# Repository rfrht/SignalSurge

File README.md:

# SignalSurge
This is an open source (check licensing [here](https://github.com/rfrht/SignalSurge/blob/main/LICENSE)) Bandpass filter for VHF and UHF amateur radio bands, with a selectable LNA and a sequencer. Designed using Eagle CAD 9.

# Why?
I live in a highly RF-polluted metropolitan area. One of these days, only FFS I have added a FM bandstop filter and I found that, contrary to my belief, my reception was **way better**! That means:

1. The front-end radio filtering is less than great (even being an expensive FT-991A)
2. Strong out of amateur band signals (and there's **plenty** of them) will desensitize your radio
3. By filtering out unwanted signals, you give more **dynamic range** to your radio, improving your reception.
4. [See for yourself here](https://www.reddit.com/r/amateurradio/comments/1gxahma/noticeable_improvement_in_ft991a_2m_rx_when_using/).

That said, the objective of this project is to remove as much as possible signals outside 2m and 70 cm bands (like: FM broadcasts, air band, commercial VHF & UHF, and everything else inbetween), ensuring that the precious front-end gain on the radio's built-in amplifier focuses on amateur band signals as much as possible.

I could buy a [300 EUR filter](https://antennas-amplifiers.com/double-2x200w-bandpass-filter-144-148mhz-430-450mhz/), but... man, that's expensive. So why not spend €3,000 worth of my own man-hours and parts to build one?

# Features
* Two **selectable** amateur band (2m and 70 cm) [bandpass filter](https://github.com/rfrht/SignalSurge/blob/main/rf-performance.md) weeds out signals, ensuring that the transceiver front-end focus its gain figures on inband signals only. That can be automated by making use of the Band Data (`TUN/LIN` port, pins `4` or `5`). Requires menu config 141 (`TUNER SELECT`) to be set as `LAMP`.
* **High performance** and selectable [low noise 15 dB amplifier](https://github.com/rfrht/SignalSurge/blob/main/rf-performance.md#amplifier-performance) (Infineon BFP460) after the bandpass filter, adding some oomph to weak signals
* Nearly **-70 dB of rejection** against the FM broadcast band
* The amplifier is **shut down when the radio is transmitting** by powering off its 5V rail (by cutting the regulator "Enable" line) to prevent any artifacts/ringing and damage. 
* Specialty RF relay allowing 50W in VHF/UHF frequencies to flow to the antenna with **low loss**, while keeping **[unparalleled isolation](https://www.reddit.com/r/rfelectronics/comments/1h5mthn/comment/m0de8n7/) (north of 60 dB)** to the downstream components
* Relay **default state (NC) is to bypass** radio directly to antenna, allowing the board to be safely powered off
* [TX Inhibit](https://github.com/rfrht/FT-991A/blob/master/understanding-ft-991a-tx-inhibit.md) logic outputs +13.8V to the FT-991A's TUN/LIN port whenever the delicate BPF/LNA chain is active, **preventing accidental** 50W transmissions into the low-power solid-state switches and filter chain
* **Static bleeding and small [surge protection](https://www.digikey.com/en/products/detail/eaton-electronics-division/0603ESDA2-TR2/3681416)** when switched to BPF/AMP
* [Via-Stitched Grounded Coplanar Waveguides (GCPW)](https://resources.altium.com/p/pros-and-cons-of-different-high-frequency-transmission-line-types) ensures strictly controlled 50-ohm impedance and suppresses parasitic radiative modes. Real-world proof: the board effortlessly handles **50 Watts** (+47 dBm) of 70cm RF on an open bench **without radiating** into the room or causing the dreaded "speaker buzz" in nearby unshielded subwoofers.
* A **[detachable miniature](https://github.com/rfrht/SignalSurge/blob/main/others/miniature-filter-board.jpg)** VHF BPF filter that [fits perfectly](https://github.com/rfrht/SignalSurge/blob/main/others/miniature-filter.jpg) in [RTL-SDR](https://www.rtl-sdr.com/rtl-sdr-com-broadcast-fm-band-stop-filter-88-108-mhz-reject-now-for-sale/) [FM bandstop cases](https://github.com/rfrht/SignalSurge/blob/main/others/encased-miniature-filter.jpg). **NOTE:** This filter DOES NOT withstand TX power; it will **fry** the inductor! Do not transmit on it.

## Library
Eagle custom component library [here](https://github.com/rfrht/FT991A-PAT/blob/master/Schematic/aarf.lbr). Ensure to **also** fetch the latest library version (and update in your Eagle) when checking out new code.

Bill of Materials (CSV format, DigiKey format) [here](https://github.com/rfrht/SignalSurge/blob/main/others/SS.csv). Notice that there's a full RF Inductor and Capacitor kit specified in the BOM - and that is **costly**. If you have the suitable RF L/C components, fine! Otherwise (like me), buy a proper one.

# Schematic: 

# Board layout
[Rev. E1 populated board](https://github.com/rfrht/SignalSurge/blob/main/others/ss-board-finished.jpg)

# BPF & Amplifier performance
Check the [test results](https://github.com/rfrht/SignalSurge/blob/main/rf-performance.md) page.

# Relay Logic
Check the [relay logic](https://github.com/rfrht/SignalSurge/blob/main/others/relay-logic.md) page.

# Test, troubleshooting steps & Specs
Yes - I have provided a [step by step testing and troubleshooting](https://github.com/rfrht/SignalSurge/blob/main/others/testing.md) guide!

# KNOWN ISSUES
**Ensure** to check the [Issues backlog](https://github.com/rfrht/SignalSurge/issues)

# JOURNEY
* Sep 18 - Updating the test figures. Successfully used the [TX INH](https://github.com/rfrht/FT-991A/blob/master/understanding-ft-991a-tx-inhibit.md) functionality at the radio. Released Rev. F.
* Sep 14 - Starting Rev. F. Changed "Bypass" and "VHF/UHF" selectors to input 5V in order to be able to use the [BCD decoders from FT-991 band data](https://hf5l.pl/en/1472-2/) at the TUN/LIN port. Added u.FL calibration pads.
* Sep 12 - Assembled board Rev. E1. Documented RF performance.
* Jun 06 - Improved UHF filter, making it narrower (50 to 30 MHz wide) and less lossy. Added another component in UHF schematic/board in order to allow for a fine tune capacitance of the coupling stage.
* May 28 - Fixed a gross error where a via shorted the VHF BPF final coupling stage. Removed ground pad on inductors at the detachable VHF BPF. Improved the radio signal trace at the first RF relay input. Updated component values for the 3-pole VHF filter (*in vivo* performed differently than the *in vitro*)
* May 04 - Replaced 3V regulator (was above its maximum rated) with a MIC5205. Removed a pulldown resistor in VHF line. Unified pulldowns on 10k and pulled lines limiters at 1k. Removed a pulldown between the NOR and AND logic ICs
* May 03 - Vibe-coded a new UHF filter with Gemini. Refactored the board, the filters, waveguides, soldermask, signal path
* May 01 - Starting Revision E. Vibe-coded a new VHF filter with Gemini
* Mar 19 - Removed two unneeded RF switches at the front-end: extra cost, complexity and insertion loss - unnecessarily, as the RF stage is handsomely isolated - and powered off during high power operations.
* Feb 28 - Found the need of a pulldown resistor in the VHF switch line. Refactored the CPW between the relays, hoping this tackle the high VSWR in 70 cm band.
* Feb 27 - Finished the board soldering, added the relays and SMA connectors. First back-to-back gain tests. First VSWR tests.
* Feb 22 - Pushing Rev. D
* Feb 20 - Finished BPF and LNA tests
* Feb/2026 - Got the Rev. C boards
* Dec 30 - Refactored the coplanar waveguides (CPW)
* Dec 29 - Changed layout of BPF section, separating inductors at 90° - Gemini said it's a good practice
* Dec 28 - Reviewed the board layout, added descriptions to signal lines, refactored the detachable VHF BPF, fixed a pernicious board cut failure to render (it was my fault)
* Dec 25 - [Used Gemini to design a VHF BPF](https://github.com/rfrht/SignalSurge/blob/main/others/gemini-prompt.md) - which yielded [pretty good results](https://github.com/rfrht/SignalSurge/blob/main/rf-performance.md), *tips hat to AI*
* Dec 25 - Starting Rev. C. 
* Aug 31 - Tested the VHF BPF and it was way out of line. Shelved the project for a while.
* Aug 31 - Added pulldown lines in comparators, routing change on the back of the board, unified logic ICs into SC70-5 footprint, updated BOM to add new pulldown resistors, better footprint for BFP460 and NCP553, fixed wrong 0.22µf part (it was 0.022µf) in BOM
* Jul 09 - Added a detachable board (taking advantage of the spare board real estate) that fits a RTL-SDR Bandpass filter. Minor signal and label revisions, routing, better labeling for signal I/O by adding expected voltages, improved semiotics. Tentatively final.
* May 18 - Fixed the Rev. A defects, check the [changelog here](https://github.com/rfrht/SignalSurge/commit/eed25a111f6a104a3589aa6e2ec3a4192e9d5c3d)
* Mar 17 - Tested relay logic (it is sound!), voltage regulators. And also fried the first board by shorting the 13.8V line on the 3V line **before** the fuse.
* Mar 16 - Tweaked the filter to bring the peak 2m BPF performance to the center of the band (146 MHz). Done in trial and error.
* Mar 11 - The boards arrived and assembled the Rev. A board - the BPF works! A bit out of frequency, but it works. More testing and component tweaking in the make.
* Feb 19 - All parts inventoried and accounted for. Placed the board order
* Feb 07 - Bought the needed parts!
* Jan/2025 - Reached the "minimally lovable project" stage.

# CHANGELOG
* Rev. F: Improved UHF BPF. Changed "Bypass" and "VHF/UHF" input selectors from 3V to 5V via resisitive divisors. Added u.FL calibration pads.
* Rev. E: Complete rewrite of VHF BPF to a proper 3-pole, improved UHF filter performance significantly, implemented a proper 50 ohm GCPW setup, re-added soldermask into the signal path, added a two-pole and three-pole test pad at the back of the board. Fixed u.FL connectors lacking connection to ground in one side. Added keep-out zones for inductors. Replaced the 3V regulator. Separated the top ground plane on north/south: The north (RF) section doesn't have any thermal relief in GND pads. The south (ancillary) section contains thermal relief GND pads.
* Rev. D: Changed 74XX pulldown lines to 100k, fixed UMD5N pin order, small tweak in UHF filter (caps changed to 20 pF). Added pulldown to VHF switch line. Rounded bypass CPW layout. Extra silkscreen. Removed exposed pads for shielding (might capacitive couple with the components). Removed unnecessary RF switches at the front-end.
* Rev. C: New VHF BPF topology, added a test UHF BPF on the back of the board, improved the LNA board layout, fixed capacitor pads (was too small)
* Rev. B: Added test points, changed connectors to SMA (big signal) and U.FL (small signal and test)
* Rev. A: Initial release

# ACKNOWLEDGEMENTS
I'd like to thank the following contributors:
* The fine [r/rfelectronics](https://www.reddit.com/r/rfelectronics/) community for helping me [square out a RX mute/isolation](https://www.reddit.com/r/rfelectronics/comments/1h0pffq/help_me_reuse_this_circuit/) (tip: it was right under my nose) issue and [how to select the large signal switch](https://www.reddit.com/r/rfelectronics/comments/1h5mthn/help_select_high_power_50w_uhf_switch/) and [a critical review of the bandpass filters](https://www.reddit.com/r/rfelectronics/comments/1hk1mgi/sanity_check_in_vhf_uhf_bpf_filters/)
* The [r/AskElectronics](https://www.reddit.com/r/AskElectronics/) community for [the sanity checking on using a PNP transistor to switch a ground signal](https://www.reddit.com/r/AskElectronics/comments/1hanp3u/will_this_switch_when_tx_gnd_is_grounded/).
* The mighty and fine [**Gordon Hudson** (AD5GG)](https://www.qrz.com/db/AD5GG) for: guiding me on component layouts, deciding for a proper impedance control, his primer on CPWs (coplanar waveguides) and assorted awesomeness.

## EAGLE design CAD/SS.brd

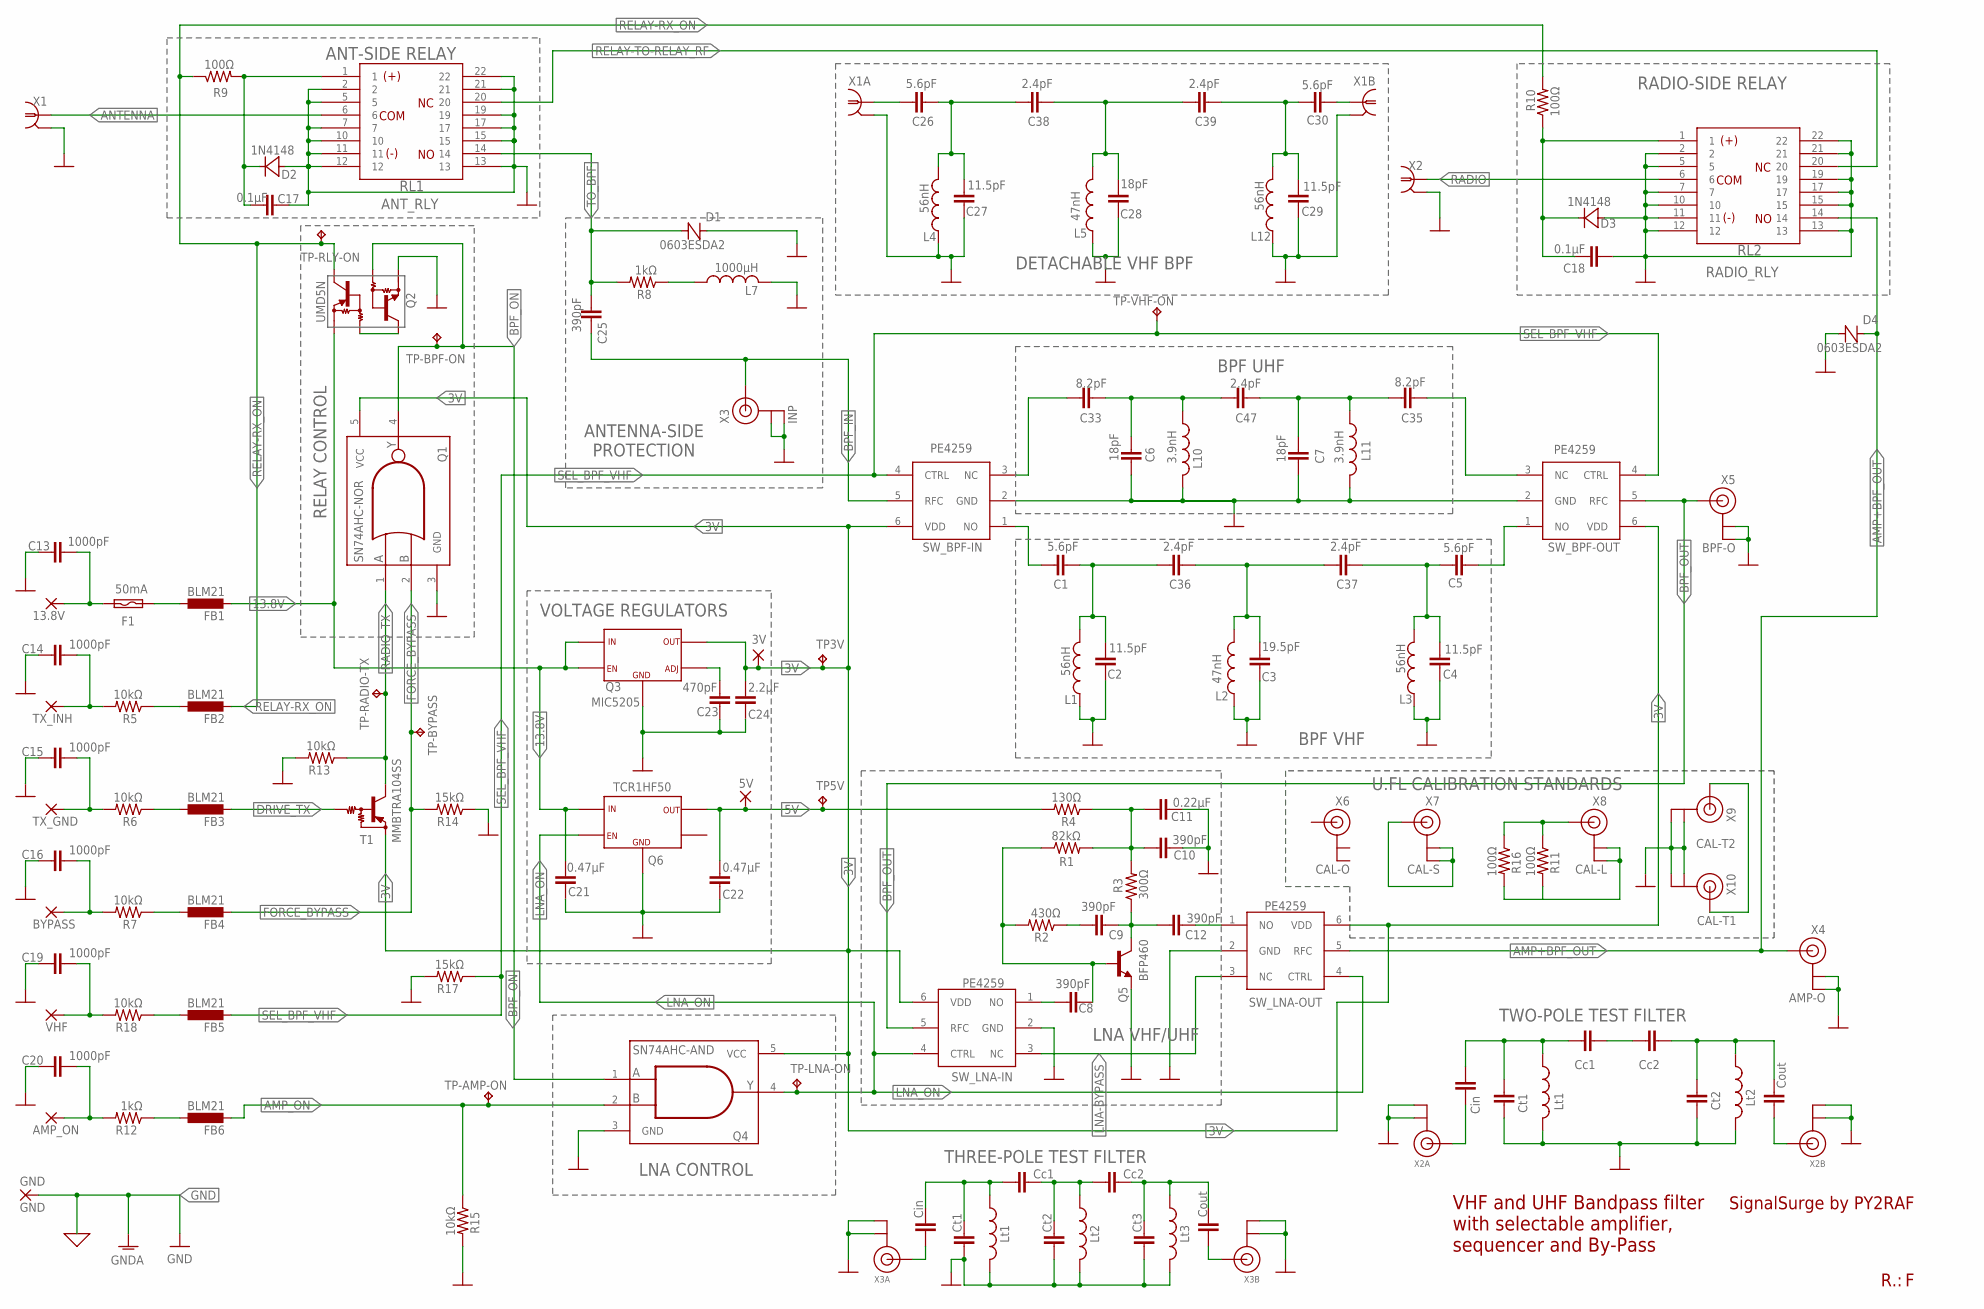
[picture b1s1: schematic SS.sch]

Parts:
3V: 3V; JUMPER1
5V: 5V; JUMPER1
13.8V: 13.8V; JUMPER1
AMP_ON: AMP_ON; JUMPER1
BYPASS: BYPASS; JUMPER1
C1, C5, C26, C30: 5.6pF; 0805
C2, C4, C27, C29: 11.5pF; 0805
C3: 19.5pF; 0805
C6, C7, C28: 18pF; 0805
C8, C9, C10, C12, C25: 390pF; 0805
C11: 0.22µF; 0805
C13, C14, C15, C16, C19, C20: 1000pF; 0805
C17, C18: 0.1µF; 0805
C21, C22: 0.47µF; 0805
C23: 470pF; 0805
C24: 2.2µF; 0805
C31, C41: Ct1; 0805
C32, C43: Ct2; 0805
C33, C35: 8.2pF; 0805
C36, C37, C38, C39, C47: 2.4pF; 0805
C40: Cin; 0805
C42: Cc1; 0805
C44: Cc2; 0805
C45: Ct3; 0805
C46: Cout; 0805
D1, D4: 0603ESDA2; 0603
D2, D3: 1N4148; SOD-323
F1: 50mA; FUSE-1206
FB1, FB2, FB3, FB4, FB5, FB6: BLM21; 0805
GND: GND; JUMPER1
L1, L3, L4, L12: 56nH; 0805
L2, L5: 47nH; 0805
L6, L16: Lt1; 0805
L7: 1000µH; 1207
L8, L17: Lt2; 0805
L9: Lt3; 0805
L10, L11: 3.9nH; 0805
L13: Cc2; 0805
L14: Cout; 0805
L15: Cin; 0805
L18: Cc1; 0805
Q1: SN74AHC-NOR; SC70-5
Q2: UMD5N; SOT363
Q3: MIC5205; SOT23-5
Q4: SN74AHC-AND; SC70-5
Q5: BFP460; SOT343R
Q6: TCR1HF50; SC-74A
R1: 82kΩ; 1206
R2: 430Ω; 1206
R3: 300Ω; 1206
R4: 130Ω; 1206
R5, R6, R7, R13, R15, R18: 10kΩ; 1206
R8, R12: 1kΩ; 1206
R9, R10, R11, R16: 100Ω; 1206
R14, R17: 15kΩ; 1206
RL1: ANT_RLY; RELAY-TE-HF3
RL2: RADIO_RLY; RELAY-TE-HF3
SW_BPF-IN: PE4259; SC-70
SW_BPF-OUT: PE4259; SC-70
SW_LNA-IN: PE4259; SC-70
SW_LNA-OUT: PE4259; SC-70
T1: MMBTRA104SS; SC59-BEC
TP3V, TP5V: TPB1,27; B1,27
TP-AMP-ON: TPB1,27; B1,27
TP-BPF-ON: TPB1,27; B1,27
TP-BYPASS: TPB1,27; B1,27
TP-LNA-ON: TPB1,27; B1,27
TP-RADIO-TX: TPB1,27; B1,27
TP-RLY-ON: TPB1,27; B1,27
TP-VHF-ON: TPB1,27; B1,27
TX_GND: TX_GND; JUMPER1
TX_INH: TX INH; JUMPER1
VHF: VHF; JUMPER1
X1: ANTENNA; SMA-RF
X1A, X1B: SMA-EDGE
X2: RADIO; SMA-RF
X2A, X2B, X3A, X3B: ANTENNA_U.FL; U.FL
X3: INP; U.FL
X4: AMP-O; U.FL
X5: BPF-O; U.FL
X6: CAL-O; U.FL
X7: CAL-S; U.FL
X8: CAL-L; U.FL
X9: CAL-T2; U.FL
X10: CAL-T1; U.FL

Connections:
3V: 3V.1, C24.P$2 (2), Q1.5 (VCC), Q3.5 (VOUT), Q4.5 (VCC), SW_BPF-IN.6 (VDD), SW_BPF-OUT.6 (VDD), SW_LNA-IN.6 (VDD), SW_LNA-OUT.6 (VDD), T1.E, TP3V.TP
5V: 5V.1, C22.P$2 (2), Q6.5 (VOUT), R4.2, TP5V.TP
13.8V: C21.P$2 (2), FB1.P$2 (2), Q2.4 (6), Q3.1 (VIN), Q3.3 (EN), Q6.1 (VIN)
13.8V_IN: 13.8V.1, C13.P$2 (2), F1.2
AMP+BPF_OUT: D4.1 (A), RL2.14, SW_LNA-OUT.5 (RFC), X4.3 (SIGNAL)
AMP_ON: FB6.P$2 (2), Q4.2 (B), R15.1, TP-AMP-ON.TP
AMP_ON_IN: AMP_ON.1, C20.P$2 (2), R12.2
ANTENNA: RL1.6, X1.1
BIAS_IN: C10.P$1 (1), C11.P$1 (1), R1.2, R3.2, R4.1
BLEED: L7.P$1 (1), R8.1
BPF_IN: C25.P$1 (1), SW_BPF-IN.5 (RFC), X3.3 (SIGNAL)
BPF_ON: Q1.4 (Y), Q2.2, Q4.1 (A), TP-BPF-ON.TP
BPF_OUT: SW_BPF-OUT.5 (RFC), SW_LNA-IN.5 (RFC), X5.3 (SIGNAL)
BYPASS_SEL_IN: BYPASS.1, C16.P$2 (2), R7.2
D-V-IN: C30.P$2 (2), X1B.P$3 (1)
D-V-OUT: C26.P$2 (2), X1A.P$3 (1)
D-V-P1: C26.P$1 (1), C27.P$1 (1), C38.P$2 (2), L4.P$2 (2)
D-V-P2: C28.P$1 (1), C38.P$1 (1), C39.P$2 (2), L5.P$2 (2)
D-V-P3: C29.P$1 (1), C30.P$1 (1), C39.P$1 (1), L12.P$1 (1)
DRIVE_TX: FB3.P$2 (2), T1.B
FEED-RA: C17.P$2 (2), D2.C, R9.2, RL1.1
FEED-RB: C18.P$1 (1), D3.C, R10.1, RL2.1
FORCE_BYPASS: FB4.P$2 (2), Q1.2 (B), R14.2, TP-BYPASS.TP
GND: C2.P$2 (2), C3.P$2 (2), C4.P$2 (2), C6.P$1 (1), C7.P$1 (1), C10.P$2 (2), C11.P$2 (2), C13.P$1 (1), C14.P$1 (1), C15.P$1 (1), C16.P$1 (1), C17.P$1 (1), C18.P$2 (2), C19.P$1 (1), C20.P$1 (1), C21.P$1 (1), C22.P$1 (1), C23.P$1 (1), C24.P$1 (1), C27.P$2 (2), C28.P$2 (2), C29.P$2 (2), C31.P$1 (1), C32.P$1 (1), C41.P$2 (2), C43.P$2 (2), C45.P$2 (2), D1.1 (A), D2.A, D3.A, D4.2 (C), GND.1, L1.P$1 (1), L2.P$1 (1), L3.P$2 (2), L4.P$1 (1), L5.P$1 (1), L6.P$2 (2), L7.P$2 (2), L8.P$2 (2), L9.P$2 (2), L10.P$2 (2), L11.P$2 (2), L12.P$2 (2), L16.P$2 (2), L17.P$2 (2), Q1.3 (GND), Q2.1, Q3.2 (GND), Q4.3 (GND), Q5.1 (E), Q5.3 (E), Q6.2 (GND), R13.2, R14.1, R15.2, R17.2, RL1.2, RL1.5, RL1.7, RL1.10, RL1.11, RL1.12, RL1.13, RL1.15, RL1.17, RL1.19, RL1.21, RL1.22, RL2.2, RL2.5, RL2.7, RL2.10, RL2.11, RL2.12, RL2.13, RL2.15, RL2.17, RL2.19, RL2.21, RL2.22, SW_BPF-IN.2 (GND), SW_BPF-OUT.2 (GND), SW_LNA-IN.2 (GND), SW_LNA-OUT.2 (GND), X1.2, X1.3 (2), X1.4 (2), X1.5 (2), X1A.P$1 (2), X1A.P$2 (2), X1A.P$4 (2), X1A.P$5 (2), X1A.P$6 (2), X1A.P$7 (2), X1B.P$1 (2), X1B.P$2 (2), X1B.P$4 (2), X1B.P$5 (2), X1B.P$6 (2), X1B.P$7 (2), X2.2, X2.3 (2), X2.4 (2), X2.5 (2), X2A.1 (GND), X2A.2 (GND), X2B.1 (GND), X2B.2 (GND), X3.1 (GND), X3.2 (GND), X3A.1 (GND), X3A.2 (GND), X3B.1 (GND), X3B.2 (GND), X4.1 (GND), X4.2 (GND), X5.1 (GND), X5.2 (GND), X9.1 (GND), X9.2 (GND), X10.1 (GND), X10.2 (GND)
LNA-BYPASS: SW_LNA-IN.3 (NC), SW_LNA-OUT.3 (NC)
LNA-IN: C8.P$2 (2), Q5.4 (B), R1.1, R2.2
LNA-OUT: C9.P$2 (2), C12.P$1 (1), Q5.2 (C), R3.1
LNA_ON: Q4.4 (Y), Q6.3 (EN), SW_LNA-IN.4 (CTRL), SW_LNA-OUT.4 (CTRL), TP-LNA-ON.TP
unnamed: C12.P$2 (2), SW_LNA-OUT.1 (NO)
unnamed: C8.P$1 (1), SW_LNA-IN.1 (NO)
unnamed: C23.P$2 (2), Q3.4 (ADJ-BYP)
unnamed: L13.P$1 (1), L18.P$2 (2)
unnamed: L15.P$1 (1), X2A.3 (SIGNAL)
unnamed: Q2.5, Q2.6 (4)
unnamed: X7.1 (GND), X7.2 (GND), X7.3 (SIGNAL)
unnamed: R11.1, R16.1, X8.3 (SIGNAL)
unnamed: R11.2, R16.2, X8.1 (GND), X8.2 (GND)
unnamed: L14.P$2 (2), X2B.3 (SIGNAL)
unnamed: FB5.P$1 (1), R18.1
unnamed: F1.1, FB1.P$1 (1)
unnamed: X9.3 (SIGNAL), X10.3 (SIGNAL)
unnamed: C9.P$1 (1), R2.1
unnamed: FB2.P$1 (1), R5.1
unnamed: FB3.P$1 (1), R6.1
unnamed: FB4.P$1 (1), R7.1
unnamed: FB6.P$1 (1), R12.1
RADIO: RL2.6, X2.1
RADIO_TX: Q1.1 (A), R13.1, T1.C, TP-RADIO-TX.TP
RELAY-RX_ON: FB2.P$2 (2), Q2.3, R9.1, R10.2, TP-RLY-ON.TP
RELAY-TO-RELAY_RF: RL1.20, RL2.20
SEL_BPF_VHF: FB5.P$2 (2), R17.1, SW_BPF-IN.4 (CTRL), SW_BPF-OUT.4 (CTRL), TP-VHF-ON.TP
T-U-IN: C40.P$1 (1), X3A.3 (SIGNAL)
T-U-OUT: C46.P$1 (1), X3B.3 (SIGNAL)
T-U-P1: C40.P$2 (2), C41.P$1 (1), C42.P$1 (1), L6.P$1 (1)
T-U-P2: C42.P$2 (2), C43.P$1 (1), C44.P$1 (1), L8.P$1 (1)
T-U-P3: C44.P$2 (2), C45.P$1 (1), C46.P$2 (2), L9.P$1 (1)
T-V-P1: C31.P$2 (2), L15.P$2 (2), L16.P$1 (1), L18.P$1 (1)
T-V-P2: C32.P$2 (2), L13.P$2 (2), L14.P$1 (1), L17.P$1 (1)
TO_BPF: C25.P$2 (2), D1.2 (C), R8.2, RL1.14
TX_GND_IN: C15.P$2 (2), R6.2, TX_GND.1
TX_INH_OUT: C14.P$2 (2), R5.2, TX_INH.1
UHF-IN: C33.P$1 (1), SW_BPF-IN.3 (NC)
UHF-OUT: C35.P$2 (2), SW_BPF-OUT.3 (NC)
UHF-P1: C6.P$2 (2), C33.P$2 (2), C47.P$1 (1), L10.P$1 (1)
UHF-P2: C7.P$2 (2), C35.P$1 (1), C47.P$2 (2), L11.P$1 (1)
VHF-IN: C1.P$2 (2), SW_BPF-IN.1 (NO)
VHF-OUT: C5.P$2 (2), SW_BPF-OUT.1 (NO)
VHF-P1: C1.P$1 (1), C2.P$1 (1), C36.P$2 (2), L1.P$2 (2)
VHF-P3: C4.P$1 (1), C5.P$1 (1), C37.P$1 (1), L3.P$1 (1)
VHF_ON_IN: C19.P$2 (2), R18.2, VHF.1
VPF-P2: C3.P$1 (1), C36.P$1 (1), C37.P$2 (2), L2.P$2 (2)

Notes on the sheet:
BPF UHF
BPF VHF
LNA VHF/UHF
RELAY CONTROL
RADIO-SIDE RELAY
VOLTAGE REGULATORS
SignalSurge by PY2RAF
R.:
VHF and UHF Bandpass filter with selectable amplifier, sequencer and By-Pass
ANTENNA-SIDE PROTECTION
LNA CONTROL
ANT-SIDE RELAY
DETACHABLE VHF BPF
TWO-POLE TEST FILTER
THREE-POLE TEST FILTER
U.FL CALIBRATION STANDARDS

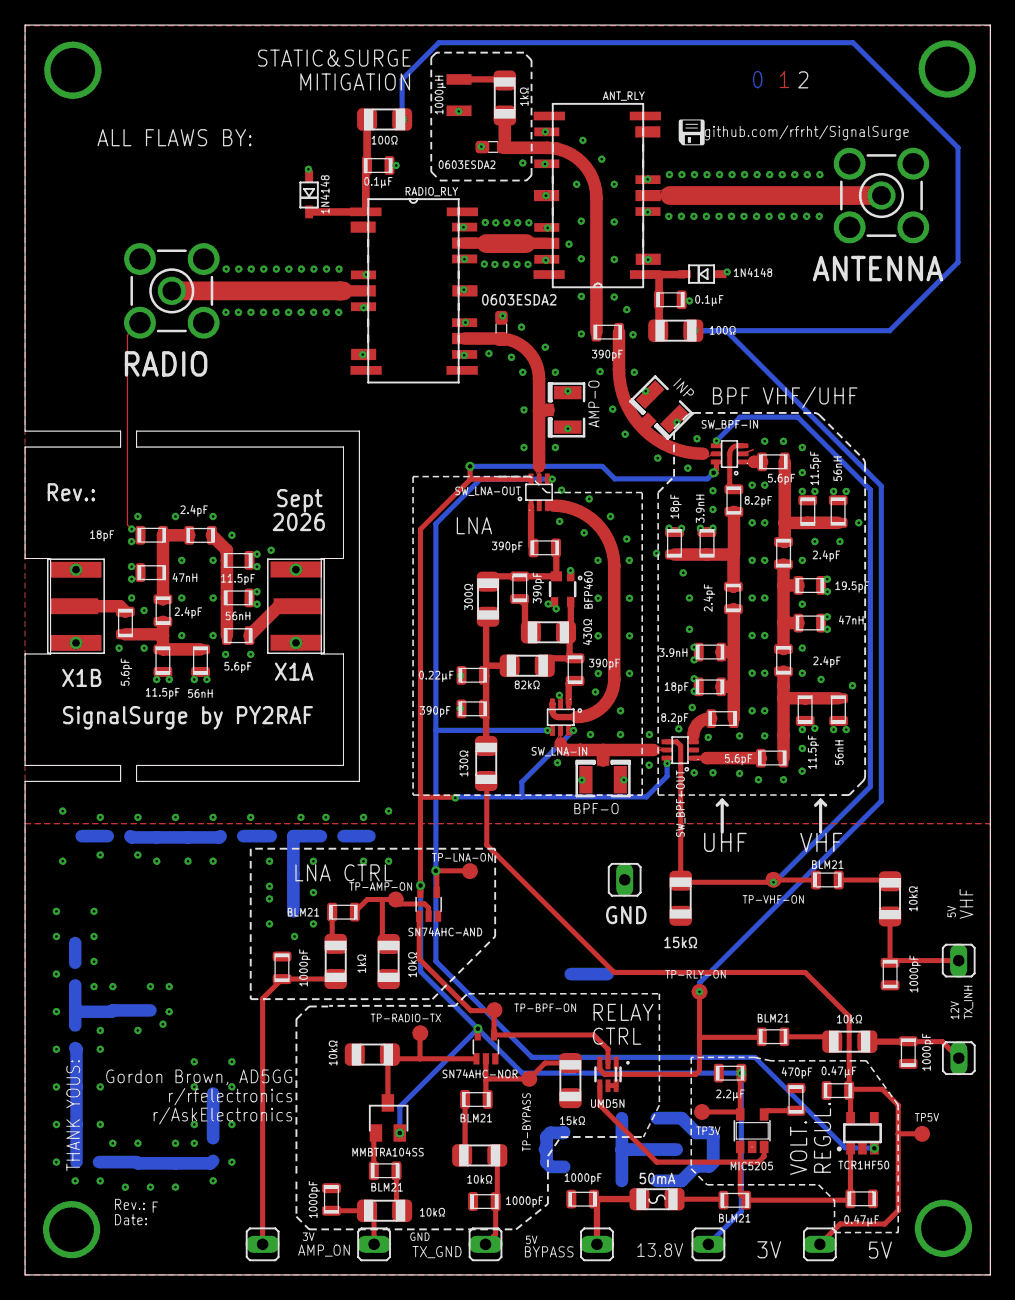
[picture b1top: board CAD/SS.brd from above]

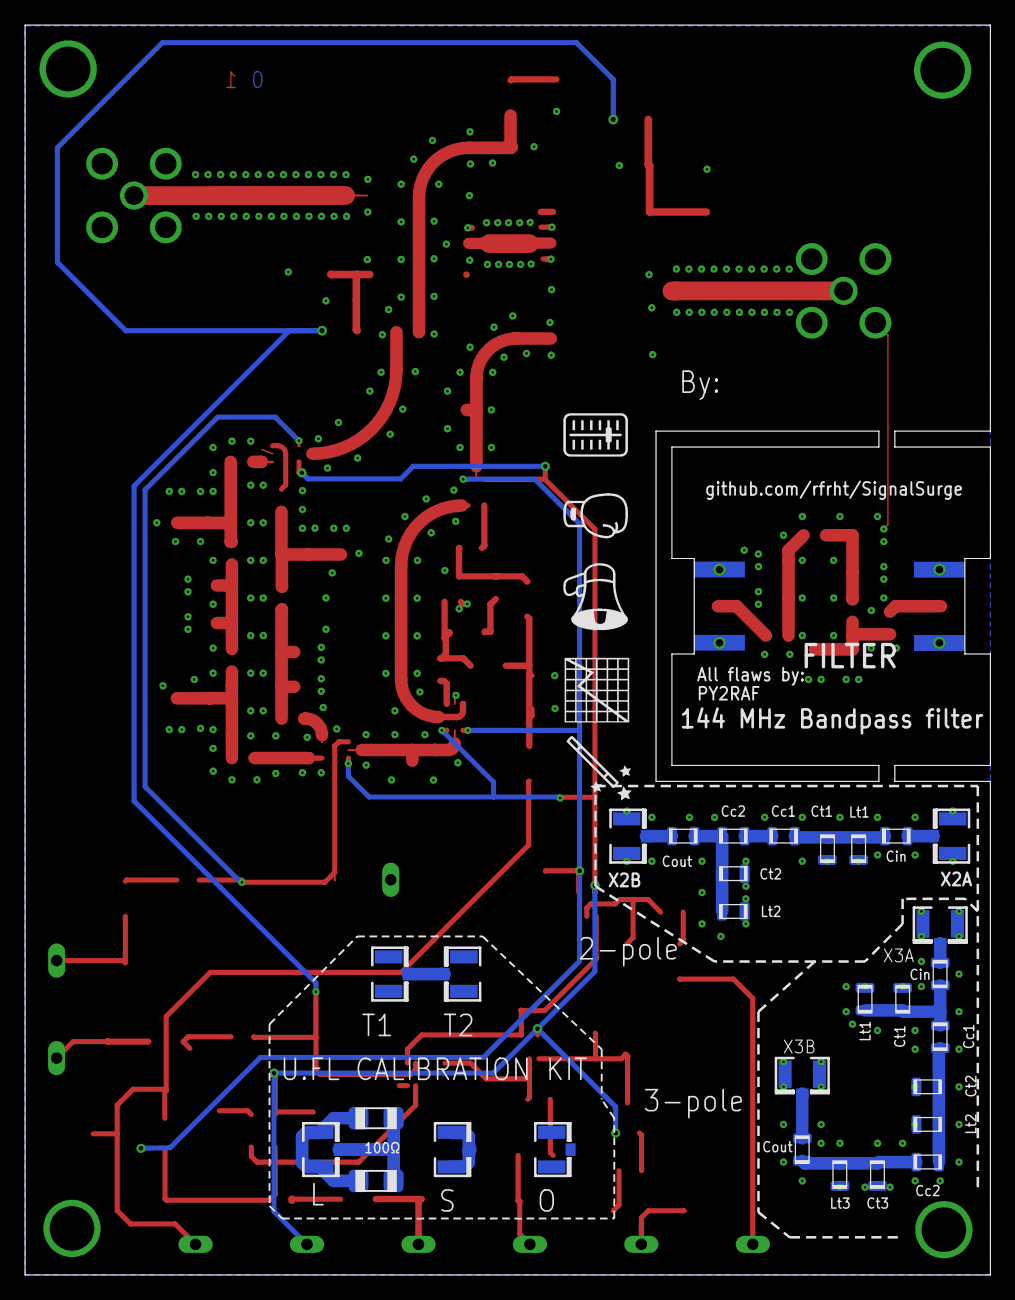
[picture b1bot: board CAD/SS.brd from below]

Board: 2 copper layers, 77.0 x 99.7 mm, 140 parts (29 on the bottom side), 71 nets.

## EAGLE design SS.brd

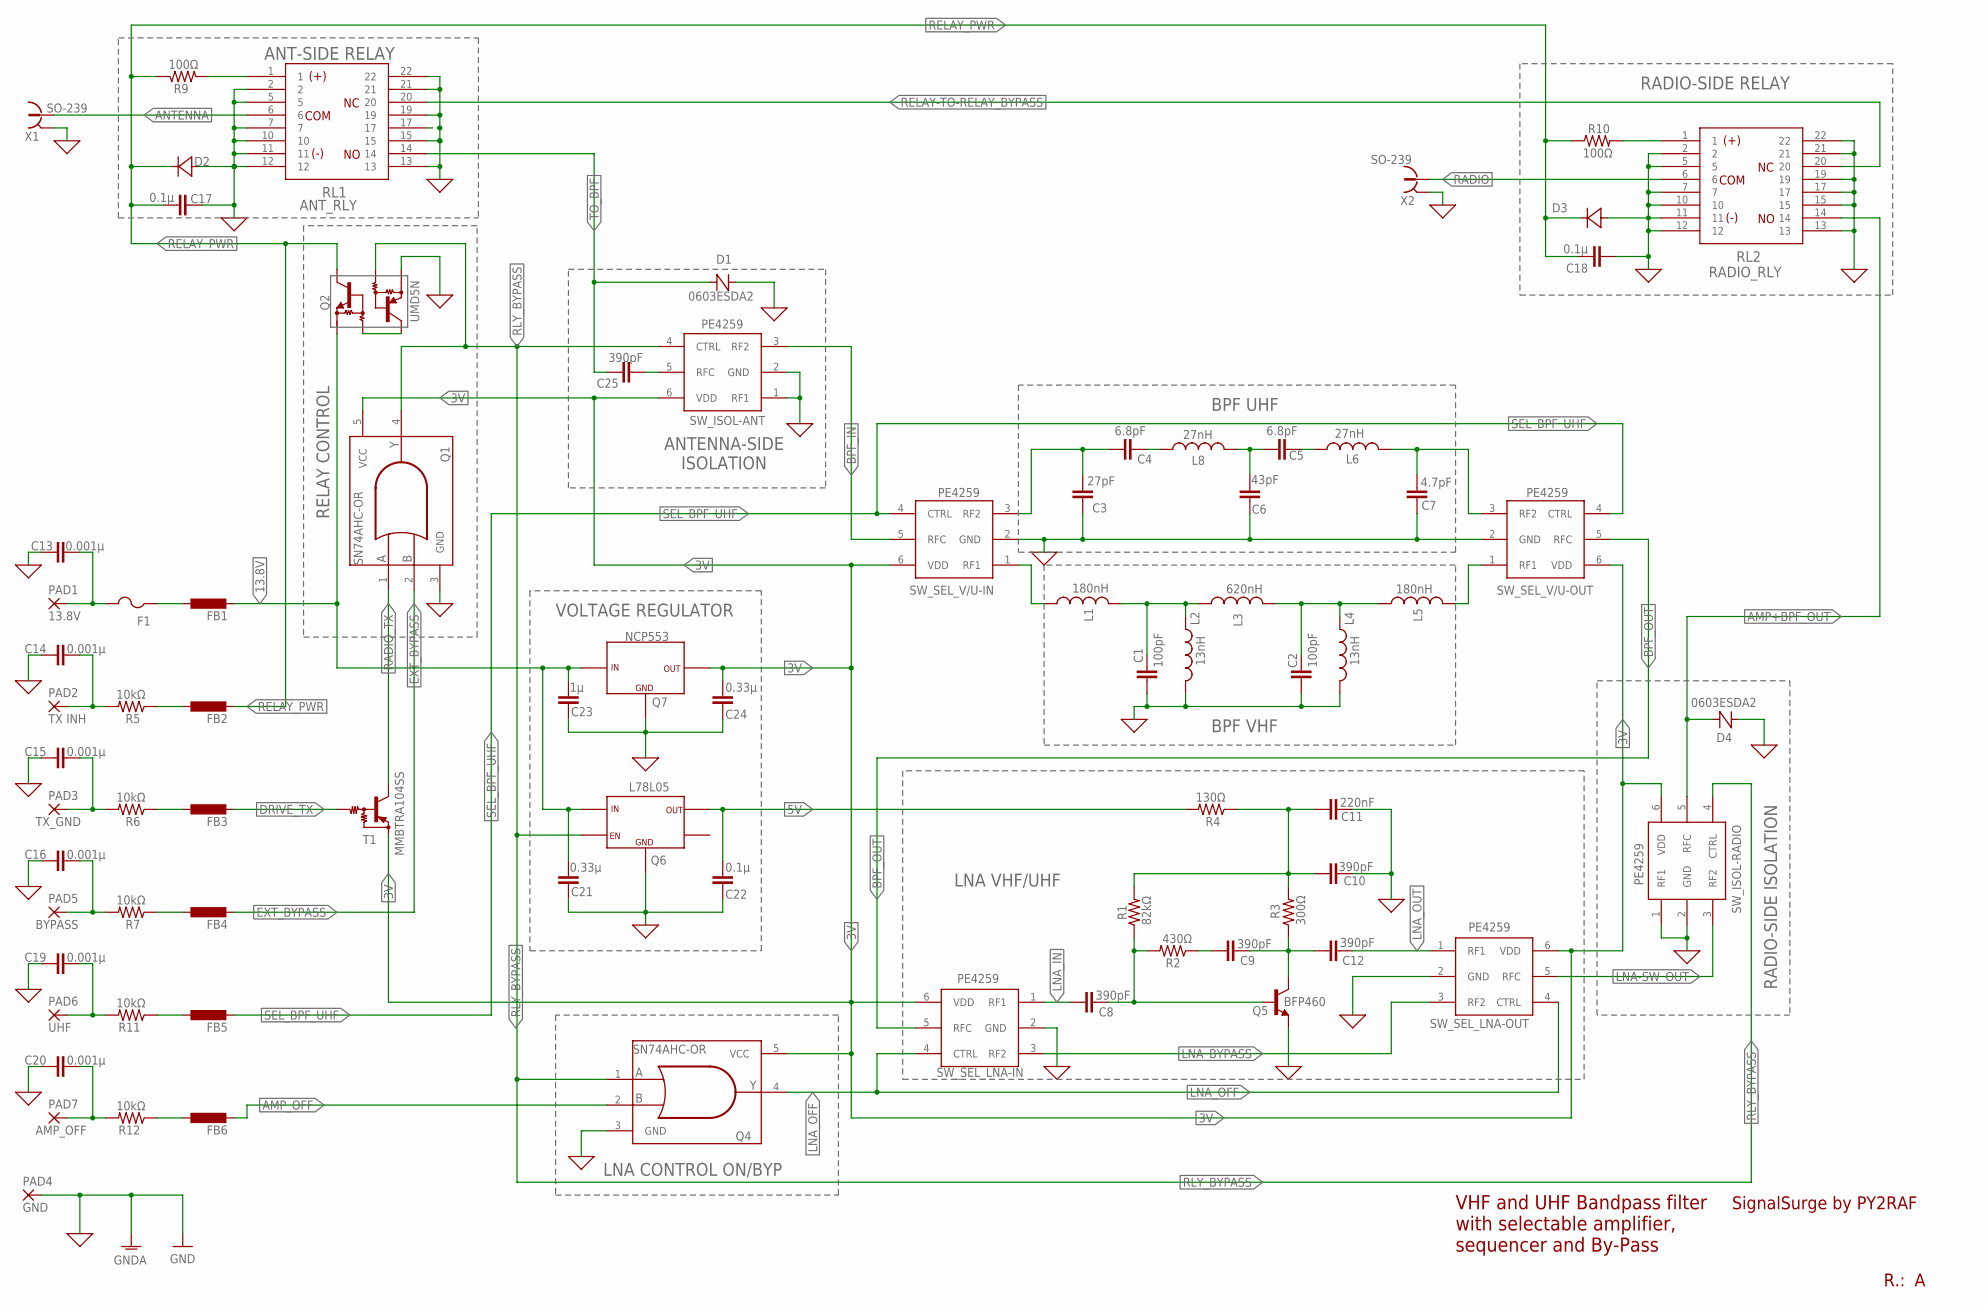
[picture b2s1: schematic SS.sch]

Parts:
C1, C2: 100pF; C0805
C3: 27pF; GRM18
C4, C5: 6.8pF; GRM18
C6: 43pF; GRM18
C7: 4.7pF; GRM18
C8, C9, C10, C12, C25: 390pF; GRM18
C11: 220nF; GRM18
C13, C14, C15, C16, C19, C20: 0.001µ; C0805
C17, C18, C22: 0.1µ; C0805
C21, C24: 0.33µ; C0805
C23: 1µ; C0805
D1, D4: 0603ESDA2; 0603
D2, D3: D-SOD323; SOD-323
F1: PTCFUSE-1206; R1206
FB1, FB2, FB3, FB4, FB5, FB6: FB-0805; 0805
L1, L5: 180nH; 0805
L2, L4: 13nH; 0805
L3: 620nH; 0805
L6, L8: 27nH; 0805
PAD1: 13.8V; SMD1,27-2,54
PAD2: TX INH; SMD1,27-2,54
PAD3: TX_GND; SMD1,27-2,54
PAD4: GND; SMD1,27-2,54
PAD5: BYPASS; SMD1,27-2,54
PAD6: UHF; SMD1,27-2,54
PAD7: AMP_OFF; SMD1,27-2,54
Q1, Q4: SN74AHC-OR; SC70-5
Q2: UMD5N; SOT363
Q5: BFP460; TSFP-3
Q6: L78L05; SOT23-5L
Q7: NCP553; SC-82AB
R1: 82kΩ; M1206
R2: 430Ω; M1206
R3: 300Ω; M1206
R4: 130Ω; M1206
R5, R6, R7, R11, R12: 10kΩ; M1206
R9, R10: 100Ω; M1206
RL1: ANT_RLY; RELAY-TE-HF3
RL2: RADIO_RLY; RELAY-TE-HF3
SW_ISOL-ANT: PE4259; SC-70
SW_ISOL-RADIO: PE4259; SC-70
SW_SEL_LNA-IN: PE4259; SC-70
SW_SEL_LNA-OUT: PE4259; SC-70
SW_SEL_V/U-IN: PE4259; SC-70
SW_SEL_V/U-OUT: PE4259; SC-70
T1: MMBTRA104SS; SC59-BEC
X1, X2: SO-239

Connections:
0: C1.1, C2.1, C3.P$1 (1), C6.P$1 (1), C7.P$1 (1), C10.P$2 (2), C11.P$2 (2), C13.1, C14.1, C15.1, C16.1, C17.1, C18.2, C19.1, C20.1, C21.1, C22.1, C23.1, C24.1, D1.1 (A), D2.A, D3.A, D4.1 (A), L2.P$2 (2), L4.P$2 (2), Q1.3 (GND), Q2.6, Q4.3 (GND), Q5.2 (E), Q6.2 (GND), Q7.1 (GN), RL1.2, RL1.5, RL1.7, RL1.10, RL1.11, RL1.12, RL1.13, RL1.15, RL1.17, RL1.19, RL1.21, RL1.22, RL2.2, RL2.5, RL2.7, RL2.10, RL2.11, RL2.12, RL2.13, RL2.15, RL2.17, RL2.19, RL2.21, RL2.22, SW_ISOL-ANT.1 (RF1), SW_ISOL-ANT.2 (GND), SW_ISOL-RADIO.1 (RF1), SW_ISOL-RADIO.2 (GND), SW_SEL_LNA-IN.2 (GND), SW_SEL_LNA-OUT.2 (GND), SW_SEL_V/U-IN.2 (GND), SW_SEL_V/U-OUT.2 (GND), X1.P$2 (2), X1.P$3 (2), X1.P$4 (2), X1.P$5 (2), X2.P$2 (2), X2.P$3 (2), X2.P$4 (2), X2.P$5 (2)
3V: C24.2, Q1.5 (VCC), Q4.5 (VCC), Q7.3 (OUT), SW_ISOL-ANT.6 (VDD), SW_ISOL-RADIO.6 (VDD), SW_SEL_LNA-IN.6 (VDD), SW_SEL_LNA-OUT.6 (VDD), SW_SEL_V/U-IN.6 (VDD), SW_SEL_V/U-OUT.6 (VDD), T1.E
5V: C22.2, Q6.5 (VOUT), R4.2
13.8V: C21.2, C23.2, FB1.P$2 (2), Q2.1, Q6.1 (VIN), Q7.2 (IN)
AMP+BPF_OUT: D4.2 (C), RL2.14, SW_ISOL-RADIO.5 (RFC)
AMP_OFF: FB6.P$2 (2), Q4.2 (B)
ANTENNA: RL1.6, X1.P$1 (1)
BPF_IN: SW_ISOL-ANT.3 (RF2), SW_SEL_V/U-IN.5 (RFC)
BPF_OUT: SW_SEL_LNA-IN.5 (RFC), SW_SEL_V/U-OUT.5 (RFC)
DRIVE_TX: FB3.P$2 (2), T1.B
EXT_BYPASS: FB4.P$2 (2), Q1.2 (B)
GND: PAD4.1
LNA-SW_OUT: SW_ISOL-RADIO.3 (RF2), SW_SEL_LNA-OUT.5 (RFC)
LNA_BYPASS: SW_SEL_LNA-IN.3 (RF2), SW_SEL_LNA-OUT.3 (RF2)
LNA_IN: C8.P$1 (1), SW_SEL_LNA-IN.1 (RF1)
LNA_OFF: Q4.4 (Y), SW_SEL_LNA-IN.4 (CTRL), SW_SEL_LNA-OUT.4 (CTRL)
LNA_OUT: C12.P$2 (2), SW_SEL_LNA-OUT.1 (RF1)
unnamed: R9.2, RL1.1
unnamed: L1.P$1 (1), SW_SEL_V/U-IN.1 (RF1)
unnamed: C3.P$2 (2), C4.P$1 (1), SW_SEL_V/U-IN.3 (RF2)
unnamed: C1.2, L1.P$2 (2), L2.P$1 (1), L3.P$1 (1)
unnamed: C25.P$2 (2), SW_ISOL-ANT.5 (RFC)
unnamed: L5.P$2 (2), SW_SEL_V/U-OUT.1 (RF1)
unnamed: C13.2, F1.2, PAD1.1
unnamed: C16.2, PAD5.1, R7.2
unnamed: C19.2, PAD6.1, R11.2
unnamed: F1.1, FB1.P$1 (1)
unnamed: C2.2, L3.P$2 (2), L4.P$1 (1), L5.P$1 (1)
unnamed: C20.2, PAD7.1, R12.2
unnamed: C15.2, PAD3.1, R6.2
unnamed: C8.P$2 (2), Q5.1 (B), R1.1, R2.2
unnamed: C4.P$2 (2), L8.P$1 (1)
unnamed: C5.P$1 (1), C6.P$2 (2), L8.P$2 (2)
unnamed: C5.P$2 (2), L6.P$1 (1)
unnamed: C7.P$2 (2), L6.P$2 (2), SW_SEL_V/U-OUT.3 (RF2)
unnamed: C9.P$1 (1), R2.1
unnamed: C10.P$1 (1), C11.P$1 (1), R1.2, R3.2, R4.1
unnamed: C9.P$2 (2), C12.P$1 (1), Q5.3 (C), R3.1
unnamed: C14.2, PAD2.1, R5.2
unnamed: FB2.P$1 (1), R5.1
unnamed: FB3.P$1 (1), R6.1
unnamed: R10.2, RL2.1
unnamed: FB4.P$1 (1), R7.1
unnamed: Q2.2, Q2.3
unnamed: FB5.P$1 (1), R11.1
unnamed: FB6.P$1 (1), R12.1
RADIO: RL2.6, X2.P$1 (1)
RADIO_TX: Q1.1 (A), T1.C
RELAY-TO-RELAY_BYPASS: RL1.20, RL2.20
RELAY_PWR: C17.2, C18.1, D2.C, D3.C, FB2.P$2 (2), Q2.4, R9.1, R10.1
RLY_BYPASS: Q1.4 (Y), Q2.5, Q4.1 (A), Q6.3 (EN), SW_ISOL-ANT.4 (CTRL), SW_ISOL-RADIO.4 (CTRL)
SEL_BPF_UHF: FB5.P$2 (2), SW_SEL_V/U-IN.4 (CTRL), SW_SEL_V/U-OUT.4 (CTRL)
TO_BPF: C25.P$1 (1), D1.2 (C), RL1.14

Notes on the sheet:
BPF UHF
BPF VHF
LNA VHF/UHF
RELAY CONTROL
RADIO-SIDE RELAY
VOLTAGE REGULATOR
SignalSurge by PY2RAF
R.:
VHF and UHF Bandpass filter with selectable amplifier, sequencer and By-Pass
ANTENNA-SIDE ISOLATION
RADIO-SIDE ISOLATION
LNA CONTROL ON/BYP
ANT-SIDE RELAY

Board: 2 copper layers, 78 parts (0 on the bottom side), 52 nets, no tracks yet.

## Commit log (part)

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2024-11-27 Add files via upload
    Initial commit - PDF, Schematic and Board.
2024-11-28 Changed the isolation circuitry
    Tip by [u/Nu2Denim/](https://www.reddit.com/user/Nu2Denim/) at [r/rfelectronics](https://www.reddit.com/r/rfelectronics/comments/1h0pffq/help_me_reuse_this_circuit/)
2024-12-02 Small minor improvements
    * Corrected position of surge arrestor
    * Added description for some networks
    * Small improvements in component placement
2024-12-10 More updates - refinements
    * Added RF relays
    * Simplified to a single relay driver (more than enough oomph to drive them both)
    * New PNP-based driver for TX_GND
    * Copious amount of signal direction and comments
2024-12-11 Progress.
    Schematic:
    * Added pulldown resistors to input ports at OR comparator
    * Added static bleeding on antenna-side isolation
    * Replaced some 1206 caps with 0805
    Board:
    * Started arranging the first components.
2024-12-11 Better directory hierarchy
2024-12-11 BPF theoretical performance figures
2024-12-11 README: BPF figures
2024-12-11 Adding: Amplifier gain figures
2024-12-11 Update README.md - Added gain figures
2024-12-14 Fix resistor feed for relays
    100R relay resistors were in a wrong place.
2024-12-14 Board: Pouring some copper over it
    Started designing the board layout.
    Plus, schematic: Fixed an error on 100R relay resistor placement
2024-12-17 More copper poured
2024-12-19 Progress
    - Replaced capacitors and resistors with ones who has a PCB marking
    - Poured more copper
    - Added annotations
    - Some block relocations
2024-12-19 New files: The first board images
2024-12-19 More progress
    - Featuring: CPWs (check https://resources.altium.com/p/pros-and-cons-of-different-high-frequency-transmission-line-types)
    - Revamped BPF component layout
    - Serious routing in RF side
    - More labeled signals
    Getting closer to the real deal
2024-12-20 Fixed crass error on LNA RF switch
    it was flipped the ports RF1/RF2 (NO/NC)
2024-12-20 Updated stuff
2024-12-20 Improved Readme
2024-12-22 Readme: More documentation
    Added relay logic part
2024-12-22 Fixed relay/switch logics
    * REviewed thoroughly the relay logic and connectors.
    * Had to add a new "NOR" part. Complexity wins...
    * Re-routed 5V regulator Enable pin to LNA logic
2024-12-22 Updated schematic.
2024-12-22 Updates to Board & Schematics
    Schematic:
    * Added pads for 3V and 5V
    Board:
    * Added signal direction on signal pads
    * Added a lot of gimmicks
    * Added exposed copper so I can try the effects of covering some RF-critical sections with copper tape
2024-12-22 Updated board image file and schematic
2024-12-22 Readme: Updated to-do list
2025-01-07 SignalSurge: Several improvements (check comment for details)
    * Changed the VHF BPF topology, using an impedance transformer to
    use a 1000 ohm-calculated BPF, yielding less critical component values
    * Small improvements in BPF CPWs
    * Implemented some changes suggested at r/rfElectronics
2025-01-07 More improvements, check the commit comment
    - Fixed BFR460 footprint (it was VERY wrong)
    - Zeroed the DRC warnings
    - Added rastnest stop on some large RF-involved components
    - Named few signal lines
    - Improved identification of Pin 1 of RF switches
    - Added Test Points
2025-01-07 New: BOM. And minor improvements (more in comments)
    - Added a BOM
    - Changed L7 footprint to match the Tayo proprietary (1207 footprint)
    - Another round of DRC check
2025-01-07 Readme: Some text repositioning
2025-01-07 Update README.md
    Added VERY important nugget
2025-02-18 Gerber: Adding initial release
2025-02-19 Board: Shrinked board a bit to fit JLCPCB $2 tier
    Board was a bit larger than 10 cm, shrinked it to fit to the $2 tier
    Also; updated README
2025-03-12 New assets: REv. A testing artifacts
2025-03-12 Added capacitor kit image
2025-03-12 Readme: Reflecting PROGRESS
2025-03-13 Fine tune README.md
    Small language improvements
2025-03-13 Another README update
2025-03-13 README: Added known issues
2025-03-18 Added test figures
2025-05-19 Update SS.csv
    Resolves #13
    Fixes:
    - Capacitor footprints
    - Brought back BLM21 from Murata
    - Fixed wrong cap values
    - Double-checked capacitor values, prices and max voltage
2025-05-19 BOM: Replaced SO239 to SMA connectors
2025-05-19 Update SS.csv
    Added u.FL connectors
    Relates to: #1
2025-05-19 Starring: Rev. B
    Resolves: #1 #2 #4 #5 #10 #11 #12 #13 #14 #15 #16 #17
    In a nutshell:
    - Fixed UMD5N placement issue
    - Improved UMD5N footprint
    - Improved NCP553 footprint
    - Improved SN74-OR footprint
2025-05-21 Fixed BOM component values
    C24 spec 0.33µF, BOM had 0.033µF
    Removed unreferenced cap C22 in 0.1µF line
2025-07-09 Revision B updates
    - Added a detachable board (taking advantage of the spare board real estate) that fits a RTL-SDR Bandpass filter.
    - Minor signal and label revisions, routing
    - Better labeling for signal I/O by adding expected voltages, improved semiotics
    - Tentatively final.
2025-07-09 Update BOM
    Added SMA Edge connectors for detachable board
2025-07-09 README: Added a note about libraries.
2025-07-10 Minor board fixes
    - Removed some vias that can be problematic around RF switches
    - Fixed silkscreen issues on I/O pads
2025-07-10 Board: Changed pads to jumpers
    Why I didn't do it before, doh. Pads are... Complicated.
    Also:
    - Changed the silk of the fuse (now with value)
    - Relabeled the region around the jumper
2025-07-14 Board: Minor improvements
    - Better GND labeling
    - Cleared area around BFP460 solder footprint
2025-07-14 Readme: Added Rev. B note
2025-08-20 Board: Fixed cut boundaries for daughterboard
    The detachable daughterboard wasn't being properly picked by
    JLCPCB (was using layer 46 to define the cut areas)
    Changed the cut sections to layer 20 and fixed it.
2025-08-31 Rev. B: Improvements
    * Added pulldown lines in comparators
    * Routing change on the back of the board
    * Unified logic ICs into SC70-5 footprint
    * Updated BOM to add new pulldown resistors - fixed wrong 0.22µf part (it was 0.022µf) in BOM
    * Better footprint for BFP460 and NCP553
2025-08-31 Readme: Terse changelog update
2025-08-31 BOM: fixed wrong 0.22µF capacitor part ID
2025-09-01 Board: Fixed cut area in daughter board
2025-12-26 BOM: Updated 390pF cap
2025-12-29 Revision C: Initial launch
    For more information, check the changelog.
2025-12-29 Update README.md
    Added link to Rev. C
2025-12-29 Update rf-performance.md
    Fixed some wrong links
2025-12-29 Update README.md
    minor nitpick
2025-12-30 Gerber: Minor fixes
    - Replaced some vias that were bleeding into the keepout zone
2025-12-30 Board: Refactored the CPWs
2025-12-30 Board image: Uploaded updated layout
2025-12-30 Update README.md
    Removed Rev. C references
2025-12-30 Update rf-performance.md
    Removed Rev. C references
2025-12-30 Files: Deprecated some, moved others, fixed references
    And also added a better picture for the theoretical VHF BPF
2025-12-30 Adding miniature filters
2025-12-30 Better images for miniature filter
2025-12-30 README: Warning for not transmit over the filter.
2025-12-31 Trimmed BFP460 simulation image
2025-12-31 Finished board: Updated image
2025-12-31 Gemini: Credits where it is due!
2025-12-31 Minor Markdown changes
    - Improved Gemini entries
    - Fixed readme PDF link
2025-12-31 Update README.md
    added link to results on journey
2025-12-31 Removed temp file
2026-02-22 Now: Revision D!
    - This is now production grade
    - Fixed the pesky UMD5N footprint issue
    - Documented thoroughly the BPF and Amplifier performance
    - Decoupled the relay logic markdown
    - Changed pulldowns on 74XX to 100kR
    - More silkscreen, ink for the win
2026-02-22 Fixed rf-performance.md
2026-02-22 Fixed and improved README.md
2026-02-22 Fixed some statements in readme
2026-02-23 Added testing documentation
2026-02-23 Updated testing.md
2026-02-23 Added specifications
    Added specifications for power consumption, signal routing, and radio frequency performance for VHF and UHF.
2026-02-23 Added 70 cm band sweep
2026-02-23 Revise section titles in README.md
    Updated section headings for clarity and consistency.
2026-02-23 Improved language and troubleshooting steps
2026-02-23 Update README with correct links for bandpass filter
2026-03-01 Revision D: improvements and corrections
    * Added a pulldown resistor in the VHF switch line.
    * Refactored the CPW between the relays, hoping this tackle the high
    VSWR found in 70 cm band.
    * Removed exposed pads that existed in previous version, that might eff up
    and cause capacitive coupling
    * Updated RF testing section
2026-03-01 Language
2026-03-19 Removed two RF switches
    Removed two unneeded RF switches at the front-end: extra cost,
    complexity and insertion loss - unnecessarily, as the RF stage
    is handsomely isolated - and powered off during high power operations.
2026-05-06 Launching: Rev. E
    * Complete rewrite of VHF BPF to a proper 3-pole ¤
    * Improved UHF filter performance significantly¤
    * Implemented a proper 50 ohm GCPW setup ¤
    * Re-added soldermask into the signal path ¤
    * Added a two-pole and three-pole test pad at the back of the board
    * Fixed u.FL connectors lacking connection to ground in one side
2026-05-18 BOM: Updated parts to sync with Rev. E
2026-05-18 BOM reordering
2026-05-29 Rev. E bug fixes
    * Added new VHF filter test figures
    * Fixed a gross error where a via shorted the VHF BPF final coupling stage
    * Removed ground pad on inductors at the detachable VHF BPF.
    * Improved the radio signal trace at the first RF relay input.
    * Updated component values for the 3-pole VHF filter (*in vivo* performed differently than the *in vitro*)
    * Updated BOM
2026-06-06 UHF filter improvements and testing figures.
2026-06-06 Updated board specs
2026-06-08 Documentation: Fixed some issues
2026-06-11 Added another series capacitor in 2 pole test filter
    The two-pole filter, used to tune/test/evaluate UHF filters sometimes
    requires a very small capacitance value. Adding a second serial coupling
    cap in case of need to put them in series to reduce capacitance and yield
    a lower value. Otherwise, jumper it with a 0 ohm chip resistor/jumper.
2026-06-14 Board: Ran a DRC and wiped out some shenanigans
